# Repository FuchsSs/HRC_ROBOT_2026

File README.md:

# HRC_ROBOT_2026

Thiết kế mạch PCB & Schematic cho xe dò line **HUST Robotic Competition 2026 (HRC 2026)** sử dụng **KiCad 10**.

## Tổng quan phần cứng
- **Vi điều khiển:** STM32F411CEU6 BlackPill
- **Driver động cơ:** TB6612FNG (hỗ trợ 2 động cơ N20 kèm encoder)
- **Nguồn:** Pin LiPo 2S (7.4V) qua XT30 (`J_BAT`), hạ áp 5V qua module Buck MP1584EN (`MP1`)
- **Cảm biến dò line:** Mảng 8+1 mắt hồng ngoại TCRT5000 bố trí cong (Kiểu 3) nối với bo chính qua cáp 12 chân (`J_IR` ↔ `J_IR_BOARD`)
- **Cảm biến bổ trợ:** IMU MPU6050 (`J_MPU` - I2C), cảm biến khoảng cách VL53L0X (`J_TOF` - I2C + XSHUT), cổng debug `UART`

## Các file chính để kiểm tra
- **KiCad Project:** `My_PCB.kicad_pro`
- **Schematic:** `My_PCB.kicad_sch` và trang con `TCRT_sensors.kicad_sch`
- **PCB (đã đi dây 2 lớp & phủ đồng GND chuẩn JLCPCB):** `My_PCB.kicad_pcb`
- **PCB (bản chỉ xếp linh kiện chưa đi dây):** `My_PCB_unrouted_pro.kicad_pcb`
- **Thư viện footprint riêng:** `customs.pretty/` và `fp-lib-table`
- **Bản xem nhanh PDF:** `schematic_perfect.pdf` và `pcb_routed_final.pdf`

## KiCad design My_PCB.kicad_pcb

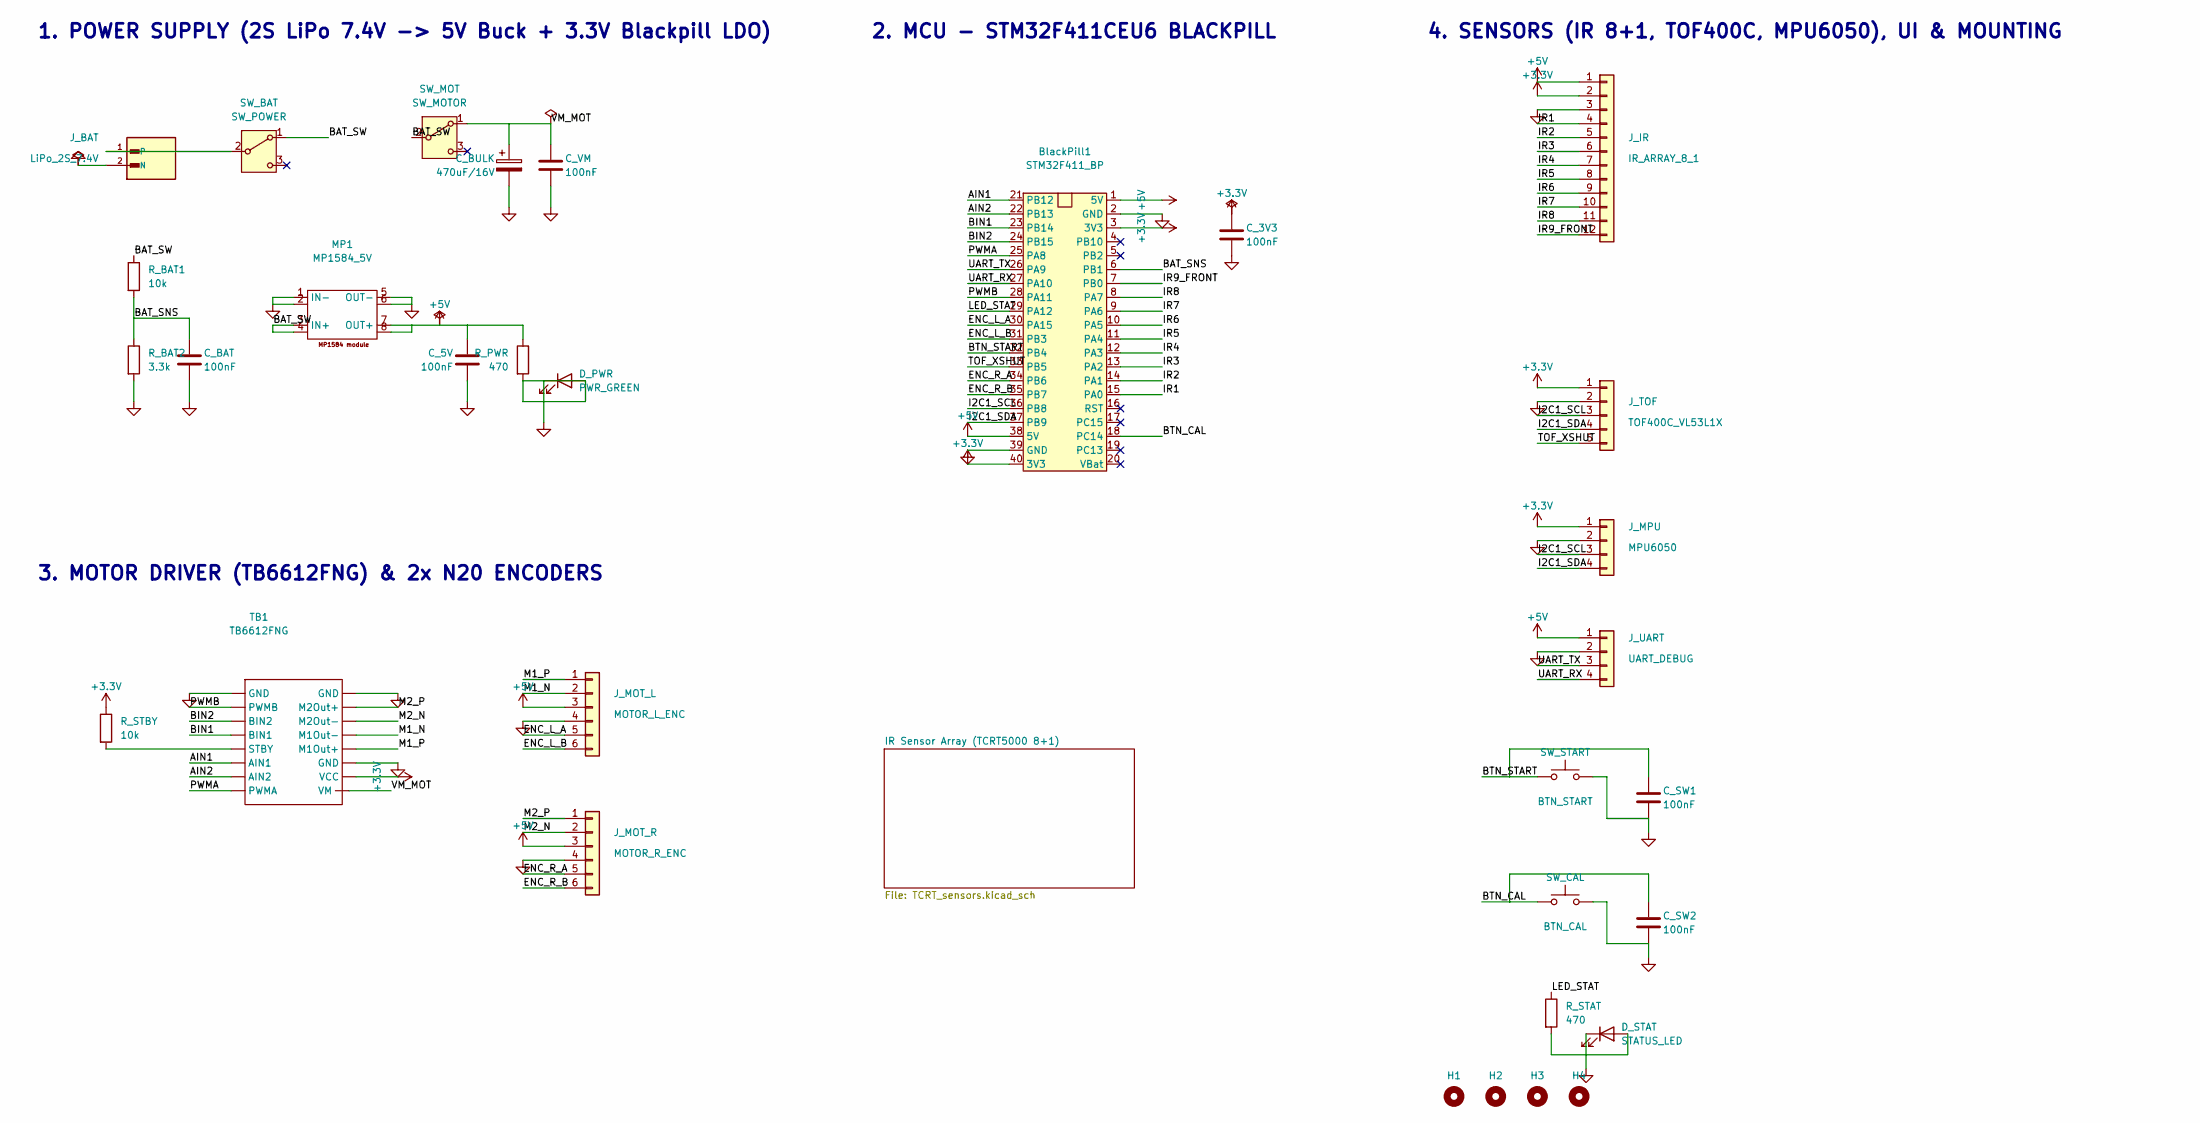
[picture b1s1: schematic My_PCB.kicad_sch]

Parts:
BlackPill1: STM32F411_BP; blackpill_fp
C_3V3, C_5V: 100nF; C_Disc_D5.0mm_W2.5mm_P5.00mm
C_BAT: 100nF; C_Disc_D5.0mm_W2.5mm_P5.00mm
C_BULK: 470uF/16V; CP_Radial_D8.0mm_P3.50mm
C_SW1, C_SW2: 100nF; C_Disc_D5.0mm_W2.5mm_P5.00mm
C_VM: 100nF; C_Disc_D5.0mm_W2.5mm_P5.00mm
D_PWR: PWR_GREEN; LED_D3.0mm
D_STAT: STATUS_LED; LED_D3.0mm
H1, H2, H3, H4: MountingHole_M2_M3; 2mm hole
J_BAT: LiPo_2S_7.4V; AMASS_XT30UPB-M_1x02_P5.0mm_Vertical
J_IR: IR_ARRAY_8_1; PinHeader_1x12_P2.54mm_Vertical
J_MOT_L: MOTOR_L_ENC; PinHeader_1x06_P2.54mm_Vertical
J_MOT_R: MOTOR_R_ENC; PinHeader_1x06_P2.54mm_Vertical
J_MPU: MPU6050; PinHeader_1x04_P2.54mm_Vertical
J_TOF: TOF400C_VL53L1X; PinHeader_1x05_P2.54mm_Vertical
J_UART: UART_DEBUG; PinHeader_1x04_P2.54mm_Vertical
MP1: MP1584_5V; MP1584_fp
R_BAT1: 10k; R_Axial_DIN0207_L6.3mm_D2.5mm_P10.16mm_Horizontal
R_BAT2: 3.3k; R_Axial_DIN0207_L6.3mm_D2.5mm_P10.16mm_Horizontal
R_PWR: 470; R_Axial_DIN0207_L6.3mm_D2.5mm_P10.16mm_Horizontal
R_STAT: 470; R_Axial_DIN0207_L6.3mm_D2.5mm_P10.16mm_Horizontal
R_STBY: 10k; R_Axial_DIN0207_L6.3mm_D2.5mm_P10.16mm_Horizontal
SW_BAT: SW_POWER; PinHeader_1x03_P2.54mm_Vertical
SW_CAL: BTN_CAL; Push button-fp
SW_MOT: SW_MOTOR; PinHeader_1x03_P2.54mm_Vertical
SW_START: BTN_START; Push button-fp
TB1: TB6612FNG; TB6612 module

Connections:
AIN1: BlackPill1.21 (PB12), TB1.6 (AIN1)
AIN2: BlackPill1.22 (PB13), TB1.7 (AIN2)
BAT_SNS: BlackPill1.6 (PB1), C_BAT.1, R_BAT1.2, R_BAT2.1
BAT_SW: MP1.3 (IN+), MP1.4, R_BAT1.1, SW_BAT.1 (A), SW_MOT.2 (B)
BIN1: BlackPill1.23 (PB14), TB1.4 (BIN1)
BIN2: BlackPill1.24 (PB15), TB1.3 (BIN2)
BTN_CAL: BlackPill1.18 (PC14), C_SW2.1, SW_CAL.1
BTN_START: BlackPill1.32 (PB4), C_SW1.1, SW_START.1
ENC_L_A: BlackPill1.30 (PA15), J_MOT_L.5
ENC_L_B: BlackPill1.31 (PB3), J_MOT_L.6
ENC_R_A: BlackPill1.34 (PB6), J_MOT_R.5
ENC_R_B: BlackPill1.35 (PB7), J_MOT_R.6
I2C1_SCL: BlackPill1.36 (PB8), J_MPU.3, J_TOF.3
I2C1_SDA: BlackPill1.37 (PB9), J_MPU.4, J_TOF.4
IR1: BlackPill1.15 (PA0), J_IR.4; also elsewhere on the board
IR2: BlackPill1.14 (PA1), J_IR.5; also elsewhere on the board
IR3: BlackPill1.13 (PA2), J_IR.6; also elsewhere on the board
IR4: BlackPill1.12 (PA3), J_IR.7; also elsewhere on the board
IR5: BlackPill1.11 (PA4), J_IR.8; also elsewhere on the board
IR6: BlackPill1.10 (PA5), J_IR.9; also elsewhere on the board
IR7: BlackPill1.9 (PA6), J_IR.10; also elsewhere on the board
IR8: BlackPill1.8 (PA7), J_IR.11; also elsewhere on the board
IR9_FRONT: BlackPill1.7 (PB0), J_IR.12; also elsewhere on the board
LED_STAT: BlackPill1.29 (PA12), R_STAT.1
M1_N: J_MOT_L.2, TB1.12 (M1Out-)
M1_P: J_MOT_L.1, TB1.13 (M1Out+)
M2_N: J_MOT_R.2, TB1.11 (M2Out-)
M2_P: J_MOT_R.1, TB1.10 (M2Out+)
unnamed: D_PWR.2 (A), R_PWR.2
unnamed: D_STAT.2 (A), R_STAT.2
unnamed: J_BAT.1, SW_BAT.2 (B)
unnamed: R_STBY.2, TB1.5 (STBY)
PWMA: BlackPill1.25 (PA8), TB1.8 (PWMA)
PWMB: BlackPill1.28 (PA11), TB1.2 (PWMB)
TOF_XSHUT: BlackPill1.33 (PB5), J_TOF.5
UART_RX: BlackPill1.27 (PA10), J_UART.4
UART_TX: BlackPill1.26 (PA9), J_UART.3

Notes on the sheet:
3. MOTOR DRIVER (TB6612FNG) & 2x N20 ENCODERS
1. POWER SUPPLY (2S LiPo 7.4V -> 5V Buck + 3.3V Blackpill LDO)
4. SENSORS (IR 8+1, TOF400C, MPU6050), UI & MOUNTING
2. MCU - STM32F411CEU6 BLACKPILL

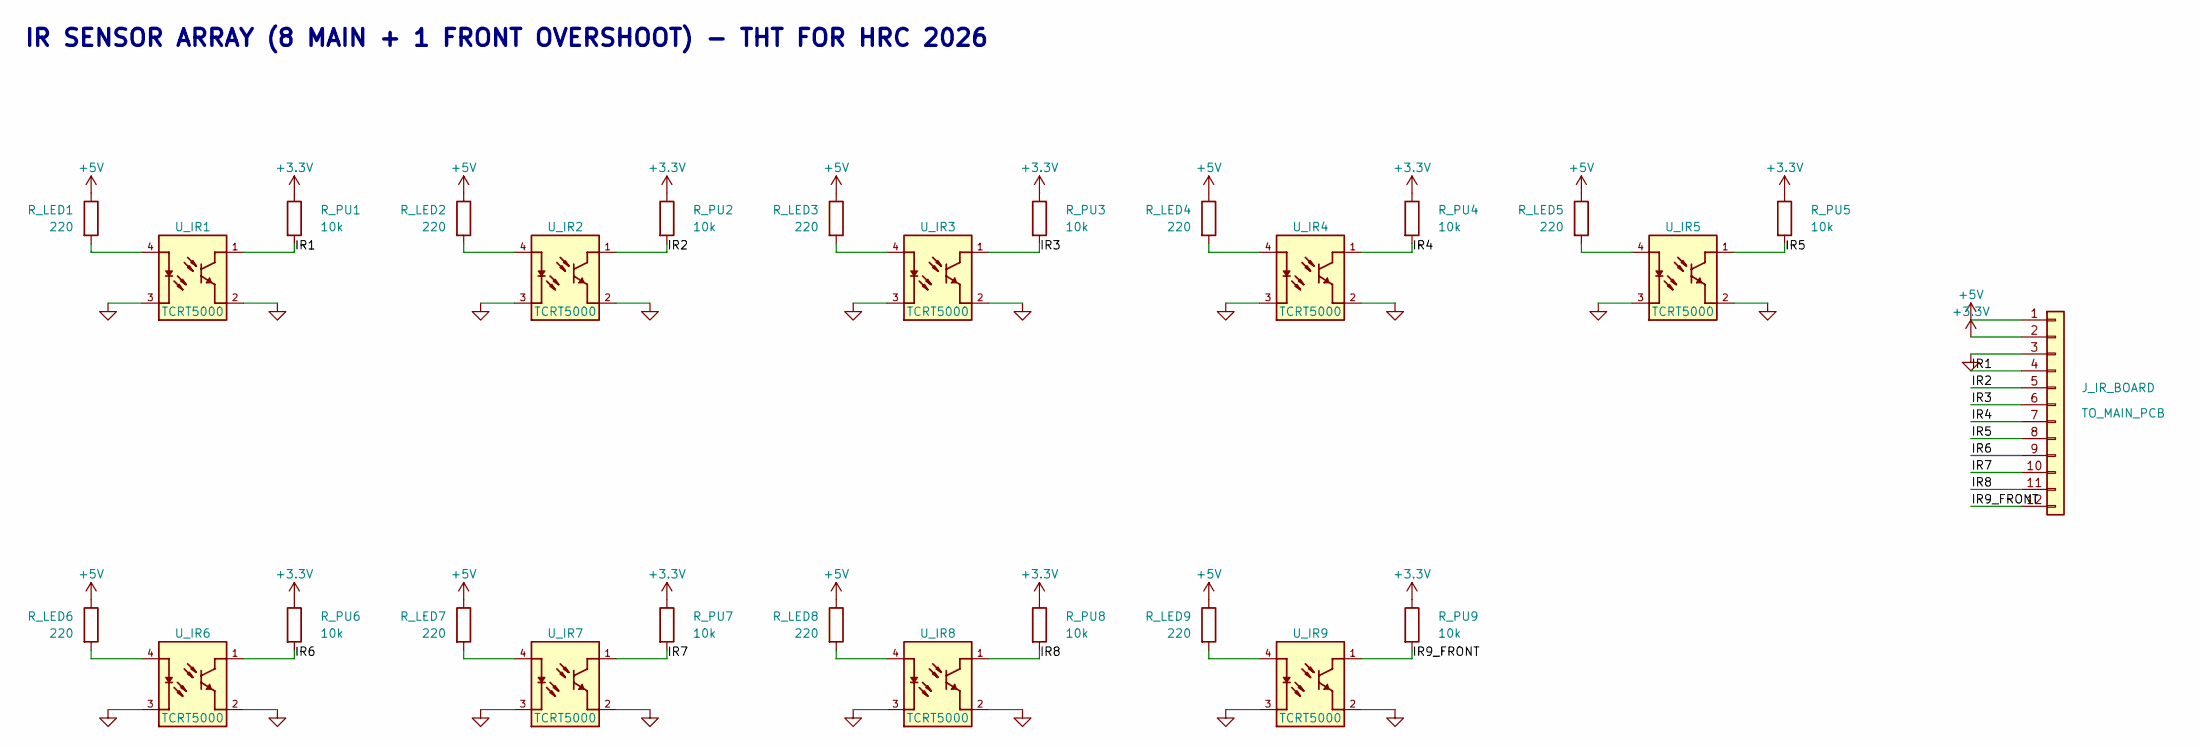
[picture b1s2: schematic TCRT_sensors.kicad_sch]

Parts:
J_IR_BOARD: TO_MAIN_PCB; PinHeader_1x12_P2.54mm_Vertical
R_LED1, R_LED2, R_LED3, R_LED4, R_LED5, R_LED6, R_LED7, R_LED8, R_LED9: 220; R_Axial_DIN0207_L6.3mm_D2.5mm_P10.16mm_Horizontal
R_PU1, R_PU2, R_PU3, R_PU4, R_PU5, R_PU6, R_PU7, R_PU8, R_PU9: 10k; R_Axial_DIN0207_L6.3mm_D2.5mm_P10.16mm_Horizontal
U_IR1, U_IR2, U_IR3, U_IR4, U_IR5, U_IR6, U_IR7, U_IR8, U_IR9: TCRT5000; XDCR_TCRT5000L

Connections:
IR1: J_IR_BOARD.4, R_PU1.2, U_IR1.1; also elsewhere on the board
IR2: J_IR_BOARD.5, R_PU2.2, U_IR2.1; also elsewhere on the board
IR3: J_IR_BOARD.6, R_PU3.2, U_IR3.1; also elsewhere on the board
IR4: J_IR_BOARD.7, R_PU4.2, U_IR4.1; also elsewhere on the board
IR5: J_IR_BOARD.8, R_PU5.2, U_IR5.1; also elsewhere on the board
IR6: J_IR_BOARD.9, R_PU6.2, U_IR6.1; also elsewhere on the board
IR7: J_IR_BOARD.10, R_PU7.2, U_IR7.1; also elsewhere on the board
IR8: J_IR_BOARD.11, R_PU8.2, U_IR8.1; also elsewhere on the board
IR9_FRONT: J_IR_BOARD.12, R_PU9.2, U_IR9.1; also elsewhere on the board
unnamed: R_LED1.2, U_IR1.4
unnamed: R_LED2.2, U_IR2.4
unnamed: R_LED3.2, U_IR3.4
unnamed: R_LED4.2, U_IR4.4
unnamed: R_LED5.2, U_IR5.4
unnamed: R_LED6.2, U_IR6.4
unnamed: R_LED7.2, U_IR7.4
unnamed: R_LED8.2, U_IR8.4
unnamed: R_LED9.2, U_IR9.4

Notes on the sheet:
IR SENSOR ARRAY (8 MAIN + 1 FRONT OVERSHOOT) - THT FOR HRC 2026

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
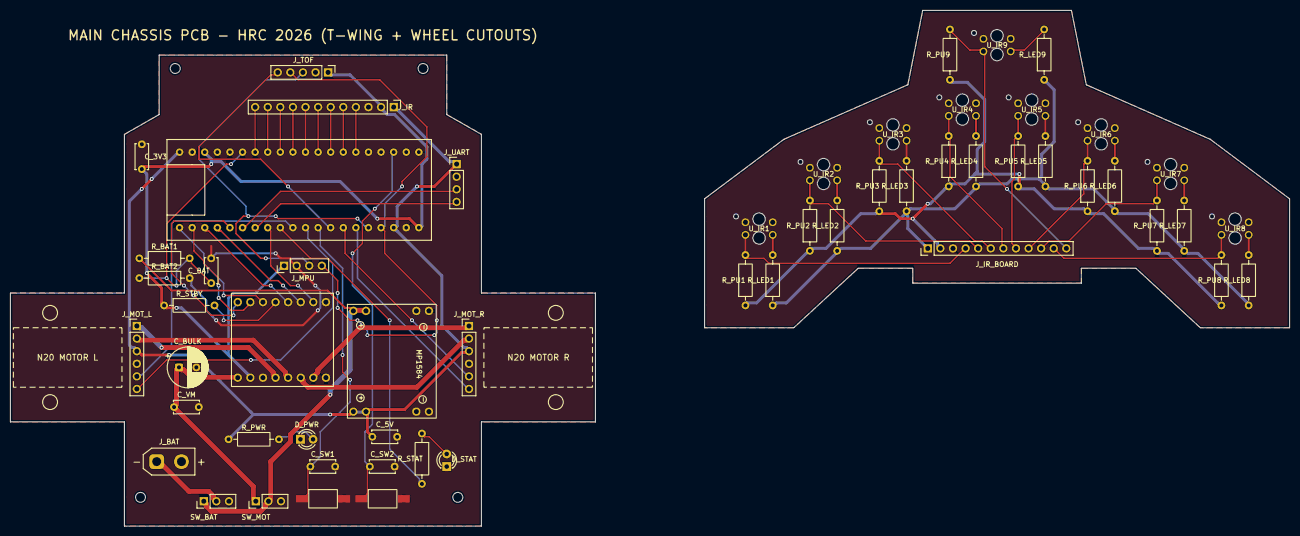
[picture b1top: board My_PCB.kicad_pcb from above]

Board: 2 copper layers, 258.0 x 104.0 mm, 60 parts (0 on the bottom side), 50 nets.
